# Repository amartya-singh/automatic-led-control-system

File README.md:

# automatic-led-control-system
Models are made using PROTEUS &amp; Ki-Cad
pins are used to provide power supply and install leds in pin.

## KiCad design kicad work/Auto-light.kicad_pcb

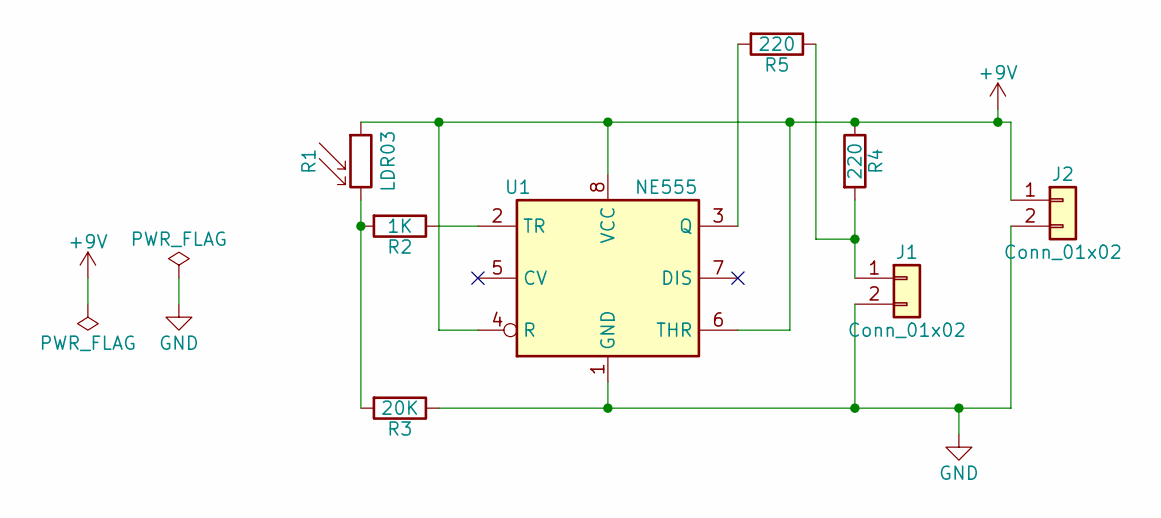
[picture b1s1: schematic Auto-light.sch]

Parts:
J1, J2: Conn_01x02; Pin_Header_Straight_1x02_Pitch2.00mm
R1: LDR03; Resistor_LDR_4.9x4.2_RM2.54
R2: 1K; R_Axial_DIN0204_L3.6mm_D1.6mm_P1.90mm_Vertical
R3: 20K; R_Axial_DIN0204_L3.6mm_D1.6mm_P1.90mm_Vertical
R4, R5: 220; R_Axial_DIN0204_L3.6mm_D1.6mm_P1.90mm_Vertical
U1: NE555; DIP-8_W7.62mm_LongPads

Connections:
+9V: J2.1, R1.1, R4.1, U1.4 (R), U1.6 (THR), U1.8 (VCC)
GND: J1.2, J2.2, R3.1, U1.1 (GND)
unnamed: J1.1, R4.2, R5.1
unnamed: R1.2, R2.2, R3.2
unnamed: R2.1, U1.2 (TR)
unnamed: R5.2, U1.3 (Q)

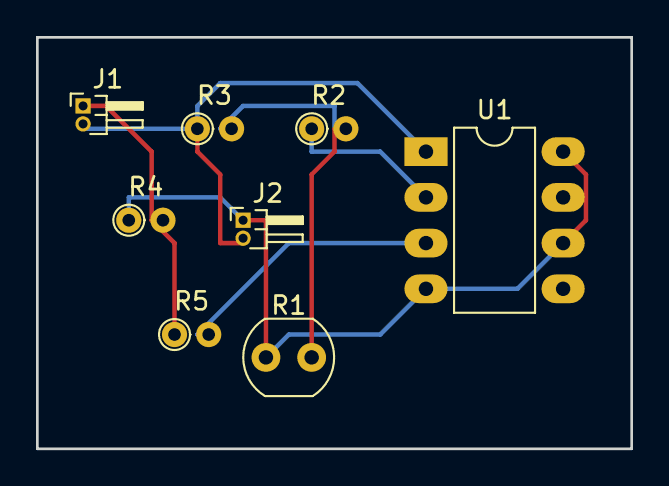
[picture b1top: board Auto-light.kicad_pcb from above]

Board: 2 copper layers, 33.0 x 22.9 mm, 8 parts (0 on the bottom side), 6 nets.

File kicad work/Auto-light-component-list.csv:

"Id";"Designator";"Package";"Quantity";"Designation";"Supplier and ref";
1;"R1";"Resistor_LDR_4.9x4.2_RM2.54";1;"LDR03";;;
2;"R2";"R_Axial_DIN0204_L3.6mm_D1.6mm_P1.90mm_Vertical";1;"1K";;;
3;"R3";"R_Axial_DIN0204_L3.6mm_D1.6mm_P1.90mm_Vertical";1;"20K";;;
4;"R4,R5";"R_Axial_DIN0204_L3.6mm_D1.6mm_P1.90mm_Vertical";2;"220";;;
5;"J1,J2";"Pin_Header_Angled_1x02_Pitch1.00mm";2;"Conn_01x02";;;
6;"U1";"DIP-8_W7.62mm_LongPads";1;"NE555";;;

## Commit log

2022-03-27 Adding Extracted files
